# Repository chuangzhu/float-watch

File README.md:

# FloatWatch
A smart watch based on [Persistence Of Vision](https://en.wikipedia.org/wiki/Persistence_of_vision).
> * Display __floating__ time in the air
> * Heart rate monitor
> * Pedometer (in progress)

## Images
#### Display

#### Appearance

#### Heart rate

#### Pedometer

#### Board

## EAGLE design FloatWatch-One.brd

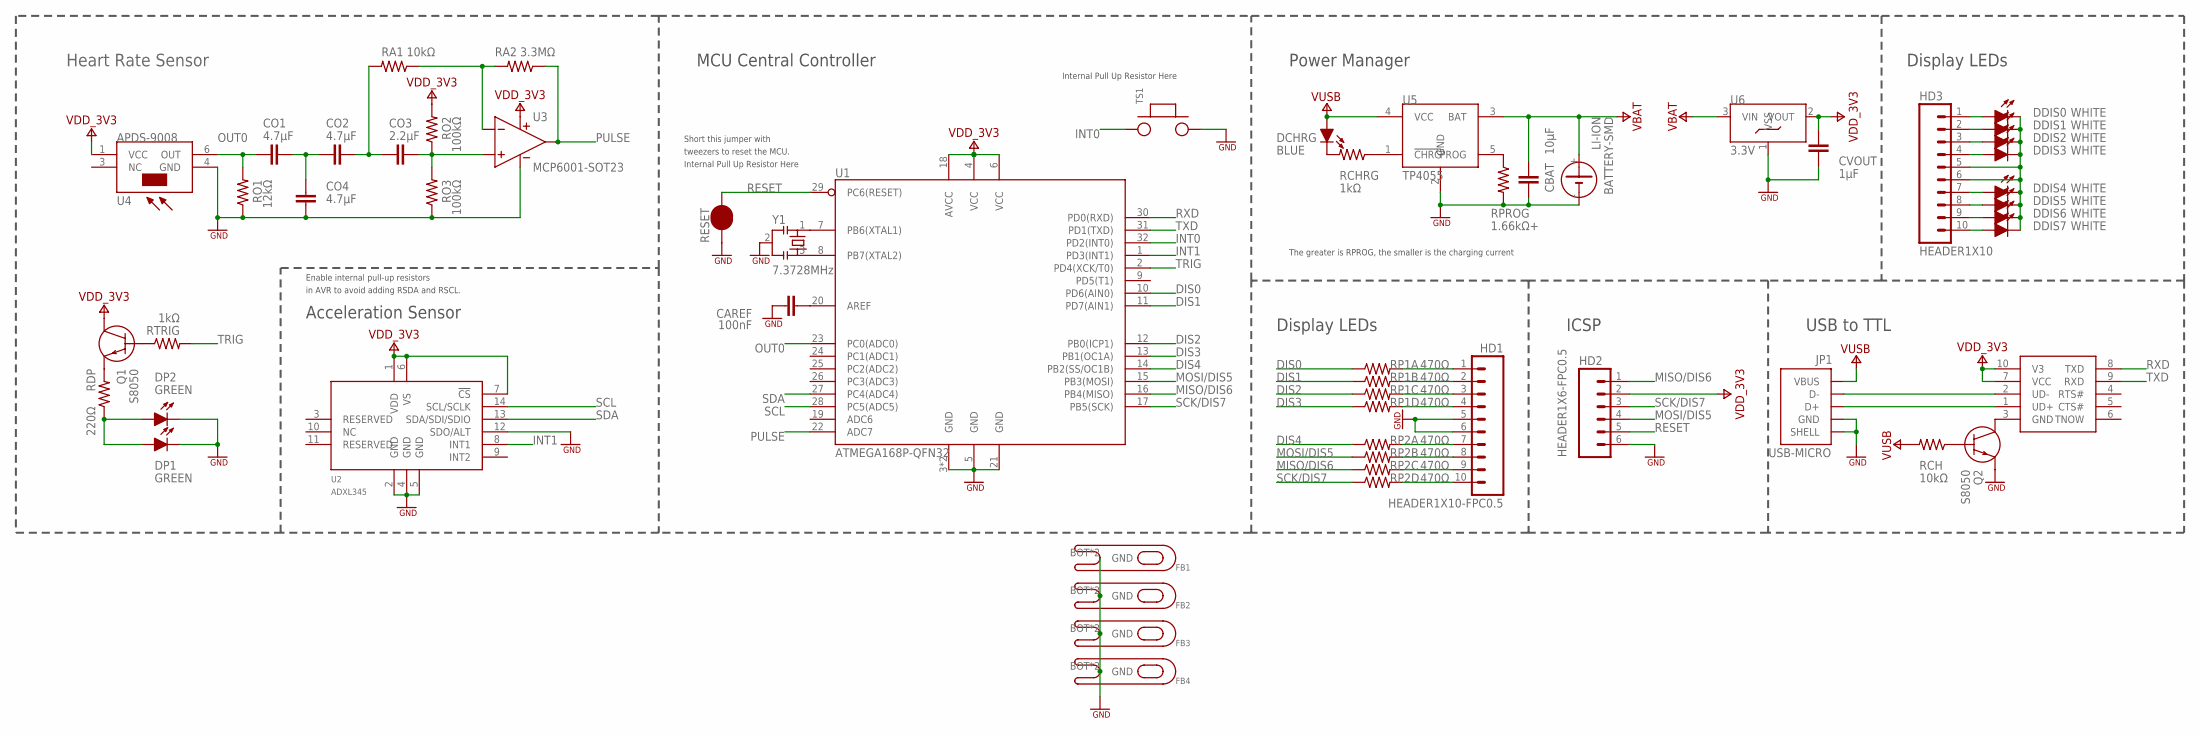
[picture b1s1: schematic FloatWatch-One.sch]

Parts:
CAREF: 100nF; SMD0603
CBAT: 10μF; SMD0603
CO1, CO2, CO4: 4.7μF; SMD0603
CO3: 2.2μF; SMD0603
CVOUT: 1μF; SMD0603
DCHRG: BLUE; LED-0603
DDIS0, DDIS1, DDIS2, DDIS3, DDIS4, DDIS5, DDIS6, DDIS7: WHITE; LED-0603
DP1, DP2: GREEN; LED-1206
FB1, FB2, FB3, FB4: BROAD-STICK; BOARD-STICK
HD1: HEADER1X10-FPC0.5; FPC0.5-10
HD2: HEADER1X6-FPC0.5; FPC0.5-6
HD3: HEADER1X10; FPC0.5-10-SOLDER
JP1: USB-MICRO
LI-ION: BATTERY-SMD; BAT-SMD
Q1, Q2: S8050; SOT23-0
RA1: 10kΩ; SMD0603
RA2: 3.3MΩ; SMD0603
RCH: 10kΩ; SMD0603
RCHRG: 1kΩ; SMD0603
RDP: 220Ω; SMD0603
RESET: JUMPER-SMD; JMPER-SMD
RO1: 12kΩ; SMD0603
RO2, RO3: 100kΩ; SMD0603
RP1, RP2: 470Ω; RP0603
RPROG: 1.66kΩ+; SMD0603
RTRIG: 1kΩ; SMD0603
TS1: TS-P; TS-3X4P
U1: ATMEGA168P-QFN32; QFN32
U2: ADXL345; LGA14
U3: MCP6001-SOT23; SOT23-5
U4: APDS-9008
U5: TP4055; SOT23-5
U6: 3.3V; SOT23-0
U7: CH340E; MSOP10
Y1: 7.3728MHz; CSTCE

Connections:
!CHRG: RCHRG.1, U5.1 (!CHRG)
!GND: DDIS0.C, DDIS1.C, DDIS2.C, DDIS3.C, DDIS4.C, DDIS5.C, DDIS6.C, DDIS7.C, HD3.5, HD3.6
AREF: CAREF.2, U1.20 (AREF)
DIS0: RP1.1, U1.10 (PD6(AIN0))
DIS1: RP1.3 (1), U1.11 (PD7(AIN1))
DIS2: RP1.5 (1), U1.12 (PB0(ICP1))
DIS3: RP1.7 (1), U1.13 (PB1(OC1A))
DIS4: RP2.1, U1.14 (PB2(SS/OC1B))
DRCHRG: DCHRG.C, RCHRG.2
GND: CAREF.1, CBAT.2, CO4.2, CVOUT.2, DP1.C, DP2.C, FB1.BOT, FB1.TOP, FB2.BOT, FB2.TOP, FB3.BOT, FB3.TOP, FB4.BOT, FB4.TOP, HD1.5, HD1.6, HD2.6, JP1.5 (GND), JP1.P1 (SHELL), JP1.P2 (SHELL), JP1.P3 (SHELL), JP1.P4 (SHELL), LI-ION.-, Q2.2 (E), RESET.1, RO1.1, RO3.1, RPROG.2, TS1.2, U1.3 (GND), U1.5 (GND), U1.21 (GND), U1.EP (GND), U2.2 (GND), U2.4 (GND), U2.5 (GND), U2.12 (SDO/ALT), U3.2 (VSS), U4.4 (GND), U5.2 (GND), U6.1 (VSS), Y1.2
GND(CH340E): Q2.3 (C), U7.3 (GND)
HD0: DDIS0.A, HD3.1
HD1: DDIS1.A, HD3.2
HD2: DDIS2.A, HD3.3
HD3: DDIS3.A, HD3.4
HD4: DDIS4.A, HD3.7
HD5: DDIS5.A, HD3.8
HD6: DDIS6.A, HD3.9
HD7: DDIS7.A, HD3.10
INT0: TS1.1, U1.32 (PD2(INT0))
INT1: U1.1 (PD3(INT1)), U2.8 (INT1)
MISO/DIS6: HD2.1, RP2.5 (1), U1.16 (PB4(MISO))
MOSI/DIS5: HD2.4, RP2.3 (1), U1.15 (PB3(MOSI))
N-IN: RA1.1, RA2.2, U3.4 (IN-)
OUT0: CO1.2, RO1.2, U1.23 (PC0(ADC0)), U4.6 (OUT)
OUT1: CO1.1, CO2.2, CO4.1
OUT2: CO2.1, CO3.2, RA1.2
P-IN: CO3.1, RO2.1, RO3.2, U3.3 (IN+)
PROG: RPROG.1, U5.5 (PROG)
PULSE: RA2.1, U1.22 (ADC7), U3.1 (OUT)
QRP: Q1.2 (E), RDP.2
RDP: DP1.A, DP2.A, RDP.1
RESET: HD2.5, RESET.2, U1.29 (PC6(RESET))
RH0: HD1.1, RP1.2
RH1: HD1.2, RP1.4 (2)
RH2: HD1.3, RP1.6 (2)
RH3: HD1.4, RP1.8 (2)
RH4: HD1.7, RP2.2
RH5: HD1.8, RP2.4 (2)
RH6: HD1.9, RP2.6 (2)
RH7: HD1.10, RP2.8 (2)
RQTRIG: Q1.1 (B), RTRIG.1
RXD: U1.30 (PD0(RXD)), U7.8 (TXD)
SCK/DIS7: HD2.3, RP2.7 (1), U1.17 (PB5(SCK))
SCL: U1.28 (PC5(ADC5)), U2.14 (SCL/SCLK)
SDA: U1.27 (PC4(ADC4)), U2.13 (SDA/SDI/SDIO)
TRIG: RTRIG.2, U1.2 (PD4(XCK/T0))
TRIGND: Q2.1 (B), RCH.1
TXD: U1.31 (PD1(TXD)), U7.9 (RXD)
UD+: JP1.3 (D+), U7.1 (UD+)
UD-: JP1.2 (D-), U7.2 (UD-)
VBAT: CBAT.1, LI-ION.+, U5.3 (BAT), U6.3 (VIN)
VDD_3V3: CVOUT.1, HD2.2, Q1.3 (C), RO2.2, U1.4 (VCC), U1.6 (VCC), U1.18 (AVCC), U2.1 (VDD), U2.6 (VS), U2.7 (!CS), U3.5 (VDD), U4.1 (VCC), U6.2 (VOUT), U7.7 (VCC), U7.10 (V3)
VUSB: DCHRG.A, JP1.1 (VBUS), RCH.2, U5.4 (VCC)
X1: U1.7 (PB6(XTAL1)), Y1.1
X2: U1.8 (PB7(XTAL2)), Y1.3

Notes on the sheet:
MCU Central Controller
Acceleration Sensor
Heart Rate Sensor
Power Manager
ICSP
Display LEDs
Enable internal pull-up resistors
in AVR to avoid adding RSDA and RSCL.
USB to TTL
Internal Pull Up Resistor Here
Short this jumper with
tweezers to reset the MCU.
The greater is RPROG, the smaller is the charging current

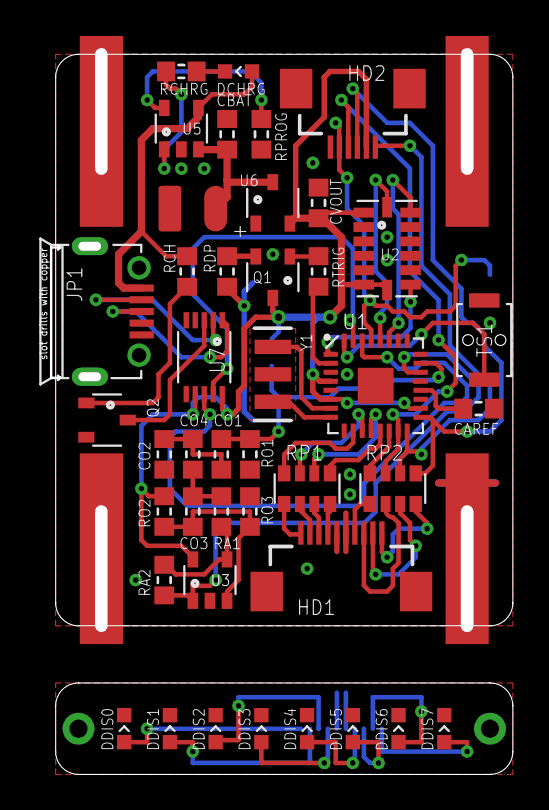
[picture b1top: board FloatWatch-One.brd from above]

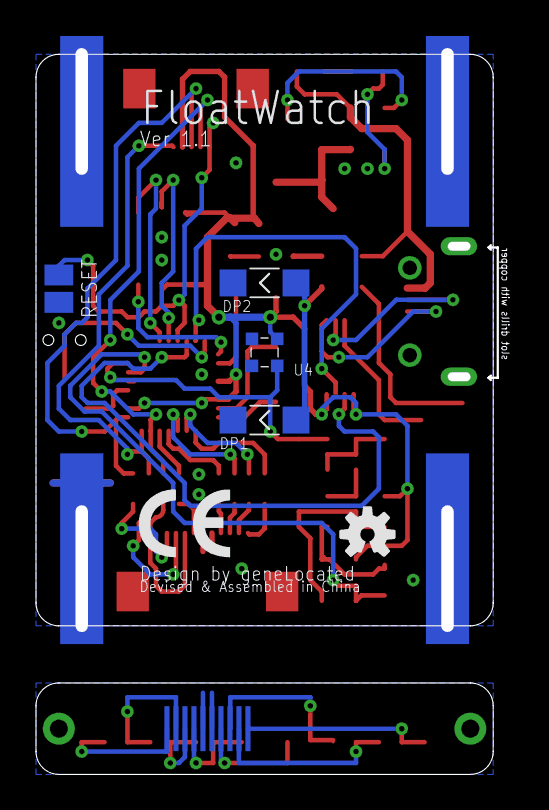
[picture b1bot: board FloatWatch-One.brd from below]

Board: 2 copper layers, 25.8 x 39.7 mm, 53 parts (7 on the bottom side), 56 nets.

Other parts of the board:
CELOGO: ICON-CE
U$1: ICON-OSHW

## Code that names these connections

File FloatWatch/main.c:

/*
 * FloatWatch.c
 *
 * Created: 2017/10/4 10:15:04
 * Author : geneLocated
 */ 

#include "main.h"

int main(void)
{
	DDRB=0x3F;	//0011 1111	(XTAL2:0, XTAL1:0, DIS7:1, DIS6:1, DIS5:1, DIS4:1, DIS3:1, DIS2:1)
	DDRD=0xD2;	//1101 0010	(DIS1:1, DIS0:1, PD5:0, TRIG:1, INT1:0, INT0:0, TXD:1, RXD:0)
	set(PORTD, INT0pin);
	//ADC_Init();
	ADXL345_Init();
	//USART_Begin();
	Clock_Init();
	TIMER0_Init();
	//comReg(0xFF);
	//set(PORTD, TRIGpin);
	sei();
    while(1)
    {
		//_delay_ms(10);
    }
}

ISR(TIMER0_OVF_vect)
{
	TCNT0=TCNT0_Init;	//这句必须保留
	{
		ADXL345_GetData();
		if(aZ<-1600)
			disStatus=0;	//允许一个周期开始显示
		if(aZ<350)
			displayTime();
		if(!(PIND & (1<<INT0pin)))
		{
			hour=12;
			minute=0;
			second=0;
		}
	}
}

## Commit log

2017-11-11 This is POVwatch 1.0
2017-11-11 This is POVwatch 1.0M
2017-11-11 This is POVwatch 1.0.1 (bugs fixed)
2017-11-11 This is POVwatch 1.1 (begin)
2017-11-11 Changed icon position
2017-11-11 Changed STICKs size to fit strap
2017-11-11 Fixed CH340E footprint bug
2017-11-11 Fix the problem that mask always broken around the crystal
2017-11-11 Fixed CH340E ground connection
2017-11-18 Rename to FloatWatch
2017-12-03 Fixes TP4055 footprint bug
2017-12-09 Fixes RPROG resistance
2018-01-06 Add files before git managed
2018-04-27 Ready for repo merge
2018-04-27 Ready for repo merge (firm)
2018-06-18 Add README
